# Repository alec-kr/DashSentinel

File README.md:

# 🚗 DashSentinel

**Real-time driver drowsiness / distraction warning prototype with an embedded feedback interface**

<table align="center">
  <tr>
    <td align="center">
      <br>
      <b>Left:</b> real-time facial tracking and attentiveness scoring
    </td>
    <td align="center">
      <br>
      <b>Right:</b> ESP8266 hardware interface
    </td>
  </tr>
</table>

## Overview

DashSentinel is a local-first driver monitoring prototype. It combines:

- OpenCV / MediaPipe FaceMesh for facial landmarks and head-pose features
- frame-quality checks for blurry, dark, overexposed, or low-contrast frames
- visibility gates for eyes and mouth so hidden landmarks do not create false drowsiness events
- multi-face selection so a passenger face does not automatically become the scored face
- optional local ONNX deep-learning fusion through OpenCV DNN
- ESP8266 telemetry for warning/status display

This project is a **warning system prototype**, not a vehicle-control or ignition-lock system. See [`docs/PRODUCT_SAFETY.md`](docs/PRODUCT_SAFETY.md).

## Current features

- Real-time face tracking and feature extraction
- Driver attentiveness scoring (%)
- Drowsiness / distraction signals based on:
  - eye closure patterns
  - yawning detection
  - head pose / looking away
  - optional local model output
  - image quality and landmark visibility
- Multi-face handling with largest/most-central driver-face selection
- Low-visibility state: `VISION DEGRADED`
- OLED display output:
  - `ALERT`
  - `WARNING`
  - `DROWSY`
  - `NO FACE`
  - `VISION DEGRADED`
- LED indicators:
  - 🟢 `ALERT` → solid green
  - 🟡 `WARNING` / `VISION DEGRADED` → blinking yellow
  - 🔴 `DROWSY` → fast blinking red
- Physical buttons:
  - reset baseline
  - reset current stats

## Why landmarks are not used alone

The scorer now gates landmarks before trusting them:

- Poor frame quality prevents high-confidence drowsiness claims.
- If eyes are not visible, EAR/blink features are ignored and the system uses head pose plus optional model output.
- If the mouth is not visible, yawning is disabled for that frame.
- Multiple detected faces are handled by selecting the most likely driver face.
- Optional local deep-learning output can be fused into the score when a model is available.

No cloud inference is used. For model setup, see [`docs/LOCAL_MODELS.md`](docs/LOCAL_MODELS.md).

## Tech stack

### Software

- Python 3
- OpenCV
- MediaPipe
- NumPy
- PySerial
- optional local ONNX model via OpenCV DNN

### Hardware

- ESP8266 (NodeMCU)
- SSD1306 OLED (I2C, 128x64)
- push buttons (x2)
- LEDs (red, yellow, green)
- resistors (3x 330 ohms)

## Project structure

```text
DashSentinel/
├── run_dashsentinel.py        # main entrypoint
├── src/
│   ├── app.py                 # main app orchestration
│   ├── cli.py                 # command-line options
│   ├── constants.py           # landmark indices
│   ├── face_selection.py      # multi-face driver-face selection
│   ├── features.py            # EAR/MAR/head-pose/visibility extraction
│   ├── local_model.py         # optional local ONNX model adapter
│   ├── logging_utils.py       # CSV event logging
│   ├── profile.py             # adaptive user baseline
│   ├── scoring.py             # scoring, gates, hysteresis
│   ├── serial_telemetry.py    # ESP8266 communication
│   └── vision_quality.py      # blur/lighting/contrast checks
├── DisplayModule/             # ESP8266 PlatformIO firmware
├── docs/                      # model and product-safety notes
├── nodemcu_carrier_pcb/       # KiCad hardware design
├── schematic/                 # schematic
├── data/                      # sample/runtime profile data
├── media/                     # screenshots/photos
├── requirements.txt
└── README.md
```

## Install

```bash
pip install -r requirements.txt
```

## Run

### UI only

```bash
python3 run_dashsentinel.py --show-ui --draw-landmarks --refine-landmarks
```

### UI + ESP8266 interface

```bash
python3 run_dashsentinel.py \
  --show-ui \
  --draw-landmarks \
  --enable-esp-serial \
  --esp-port /dev/ttyUSB0
```

### Headless mode with logging

```bash
python3 run_dashsentinel.py \
  --headless \
  --log-csv \
  --enable-esp-serial \
  --esp-port /dev/ttyUSB0
```

### Higher-resolution camera input

For unclear frames, try a better camera or a higher input resolution if your machine can keep up:

```bash
python3 run_dashsentinel.py --show-ui --width 960 --height 540 --camera-fps 30
```

### Optional local model

```bash
python3 run_dashsentinel.py \
  --show-ui \
  --max-faces 3 \
  --local-model-path ./models/dms_classifier.onnx \
  --local-model-input-size 224
```

## Calibration

At startup, DashSentinel collects a user-specific baseline from frames that pass quality and visibility checks. Baseline frames must have:

- usable frame quality
- visible eyes and mouth
- no yawn flag
- no bad posture flag
- low eye-closure duration

Reset baseline manually:

```bash
python3 run_dashsentinel.py --show-ui --mirror --rebuild-baseline-on-start
```

## Useful flags

```bash
python3 run_dashsentinel.py --help
```

Important robustness flags:

- `--max-faces 3`
- `--min-frame-brightness 35`
- `--max-frame-brightness 225`
- `--min-frame-contrast 18`
- `--min-frame-blur 45`
- `--low-quality-hold-frames 8`
- `--local-model-path ./models/dms_classifier.onnx`
- `--require-local-model`

## Safety note

DashSentinel should warn, log, and display status only. It should not disable a vehicle, block emergency use, or make enforcement/lockout decisions from computer vision alone. See [`docs/PRODUCT_SAFETY.md`](docs/PRODUCT_SAFETY.md).

## Future improvements

- train and validate a local DMS model on in-car lighting/camera conditions
- identity tracking / enrolled-driver selection over time
- camera calibration and night-driving validation
- sunglasses/mask/glare robustness tests
- more formal evaluation metrics for false positives/false negatives
- mobile app integration
- standalone embedded unit / dashcam form factor

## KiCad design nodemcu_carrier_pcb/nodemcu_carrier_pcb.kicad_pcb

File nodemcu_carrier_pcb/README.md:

## NodeMCU ESP-12E carrier board for DashSentinel external display/status module.

Features:
- Amica-style NodeMCU ESP-12E footprint, 22.86 mm / 0.9 in header spacing
- 4-pin I2C OLED connector: GND, VCC, SCL, SDA
- 3 status LEDs: green/yellow/red
- 2 push buttons
- Through-hole components for easy hand soldering

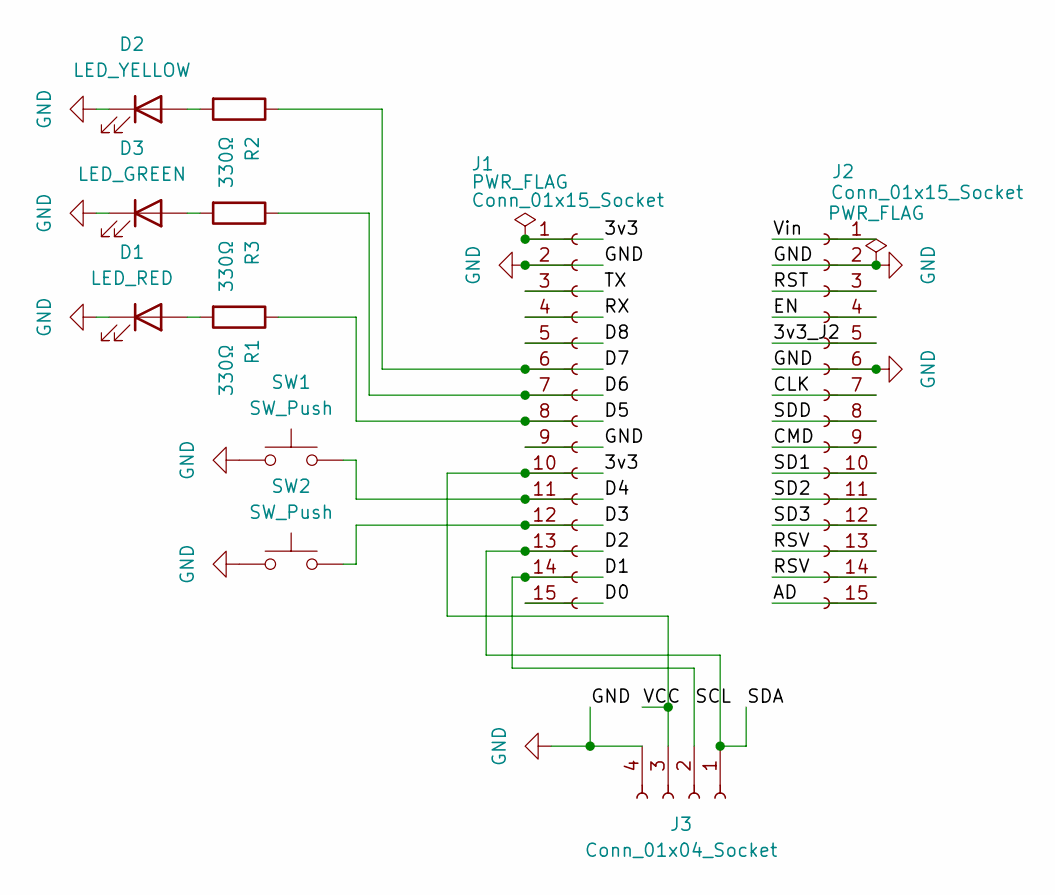
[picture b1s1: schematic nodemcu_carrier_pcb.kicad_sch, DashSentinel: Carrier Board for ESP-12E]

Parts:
D1: LED_RED; LED_D3.0mm
D2: LED_YELLOW; LED_D3.0mm
D3: LED_GREEN; LED_D3.0mm
J1, J2: Conn_01x15_Socket; PinSocket_1x15_P2.54mm_Vertical
J3: Conn_01x04_Socket; PinSocket_1x04_P2.54mm_Vertical
R1, R2, R3: 330Ω; R_Axial_DIN0207_L6.3mm_D2.5mm_P7.62mm_Horizontal
SW1, SW2: SW_Push; SW_PUSH_6mm

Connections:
/3v3: J1.1, J1.10, J3.3
/3v3_J2: J2.5
/AD: J2.15
/CLK: J2.7
/CMD: J2.9
/D0: J1.15
/D1: J1.14, J3.2
/D2: J1.13, J3.1
/D3: J1.12, SW2.2
/D4: J1.11, SW1.2
/D5: J1.8, R1.1
/D6: J1.7, R3.1
/D7: J1.6, R2.1
/D8: J1.5
/EN: J2.4
/RST: J2.3
/RSV: J2.13, J2.14
/RX: J1.4
/SD1: J2.10
/SD2: J2.11
/SD3: J2.12
/SDD: J2.8
/TX: J1.3
/Vin: J2.1
GND: D1.1 (K), D2.1 (K), D3.1 (K), J1.2, J1.9, J2.2, J2.6, J3.4, SW1.1, SW2.1
unnamed: D1.2 (A), R1.2
unnamed: D2.2 (A), R2.2
unnamed: D3.2 (A), R3.2

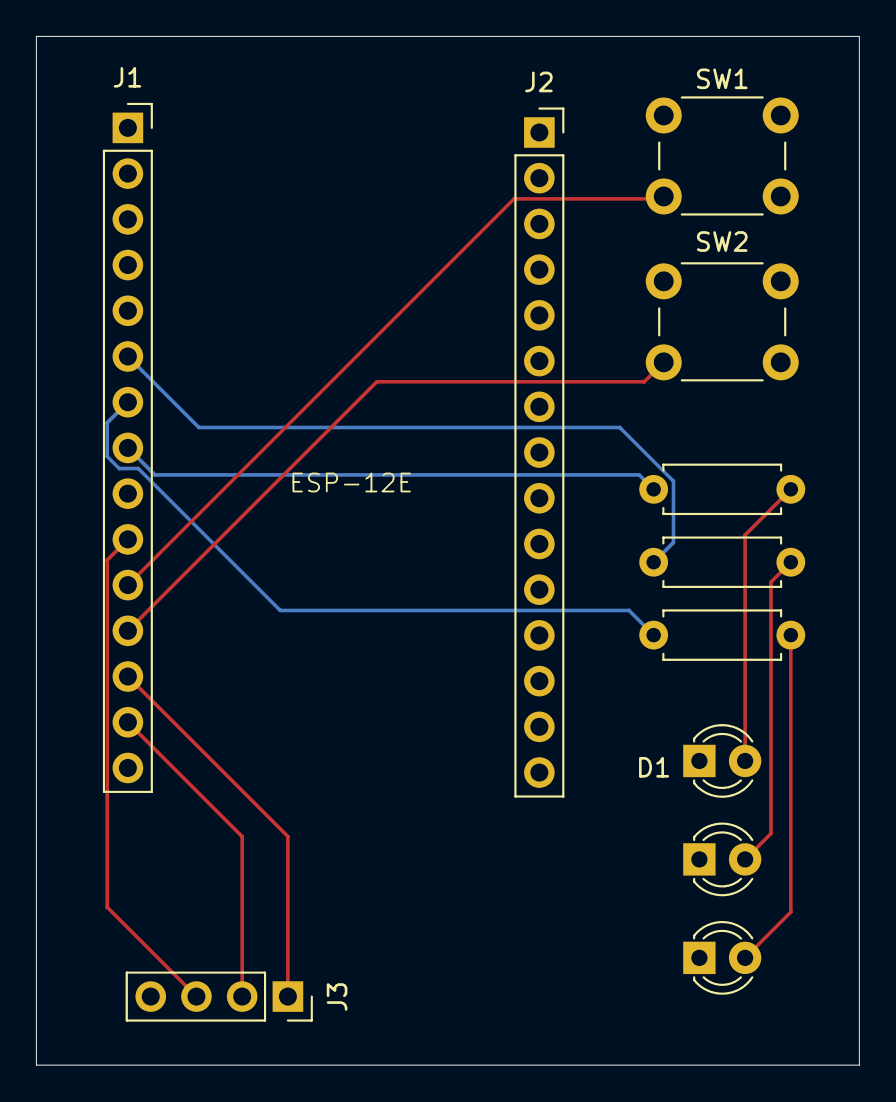
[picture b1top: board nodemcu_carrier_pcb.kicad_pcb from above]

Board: 2 copper layers, 45.7 x 57.2 mm, 11 parts (0 on the bottom side), 13 nets.

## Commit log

2026-04-16 Update README with project details and features
    updated readme with first-time content
2026-04-18 Add all required files via upload
2026-04-18 Update README with usage instructions
    Added usage instructions for running the application.
2026-04-18 Update README with testing hardware details
    Added information about testing on Intel N100 and NVIDIA Jetson Orin Nano.
2026-04-20 Update tested devices in README
2026-04-22 Update README with MediaPipe requirements
    Added note about MediaPipe requirements for Raspberry Pi.
2026-04-26 Implement base ESP8266 DisplayModule logic.
    Implemented base ESP8266 DisplayModule logic. Includes PlatformIO env and code for receiving and displaying the status, and percentage alert/drowsy.
2026-04-26 Added WIP flag to readme
2026-04-26 Added basic workflow for DisplayModule validation
2026-04-26 workflow cleanup for DisplayModule
2026-04-26 Upgrade to v5 actions
2026-04-27 add Python CI workflow
2026-04-27 Updated DisplayModule workflow to include firmware upload
2026-04-27 add workflow flag
2026-04-27 modified gitignore to exclude pio and vscode folders
2026-04-29 added button functionality and reset logic
2026-04-30 Added comments and fixed readme
2026-04-30 Revise README structure and content
    Removed work-in-progress notes and updated section headers.
2026-04-30 Enhanced model to better weight-in the head position
2026-04-30 Add Pylint workflow for Python code analysis
2026-04-30 Fixed whitespace and long lines in app.py
2026-04-30 Fixed some pylint issues
2026-04-30 Revise Python versions and update setup actions
    Updated Python versions and improved setup steps.
2026-04-30 Add pylint installation to workflow
2026-04-30 fixed pylint errors
2026-04-30 modified pylint to exclude cv2 member warnings
2026-04-30 fixing pylint errors
2026-04-30 fixing mediapipe pylint issue
2026-04-30 remove pylint for v3.9
2026-04-30 Added logic for 3 LEDs
2026-05-01 Added support for LEDs
2026-05-01 Add esp12e carrier board hardware design
2026-05-01 Update kicad schema
2026-05-01 Added screenshots and schematics
2026-05-01 Enhance README with images and feature descriptions
    Added images and descriptions for the system's features.
2026-05-10 Rename driver_profile.json to sample_driver_profile.json
    Changing filename to prevent users from having to rebuild baseline on first run.
2026-05-13 Specify mediapipe version in requirements.txt
    Specify mediapipe version as new API has moved from ```solutions``` to ```tasks```
2026-05-20 Add additional status and upgrade model
2026-05-20 Fixed pylint issues
